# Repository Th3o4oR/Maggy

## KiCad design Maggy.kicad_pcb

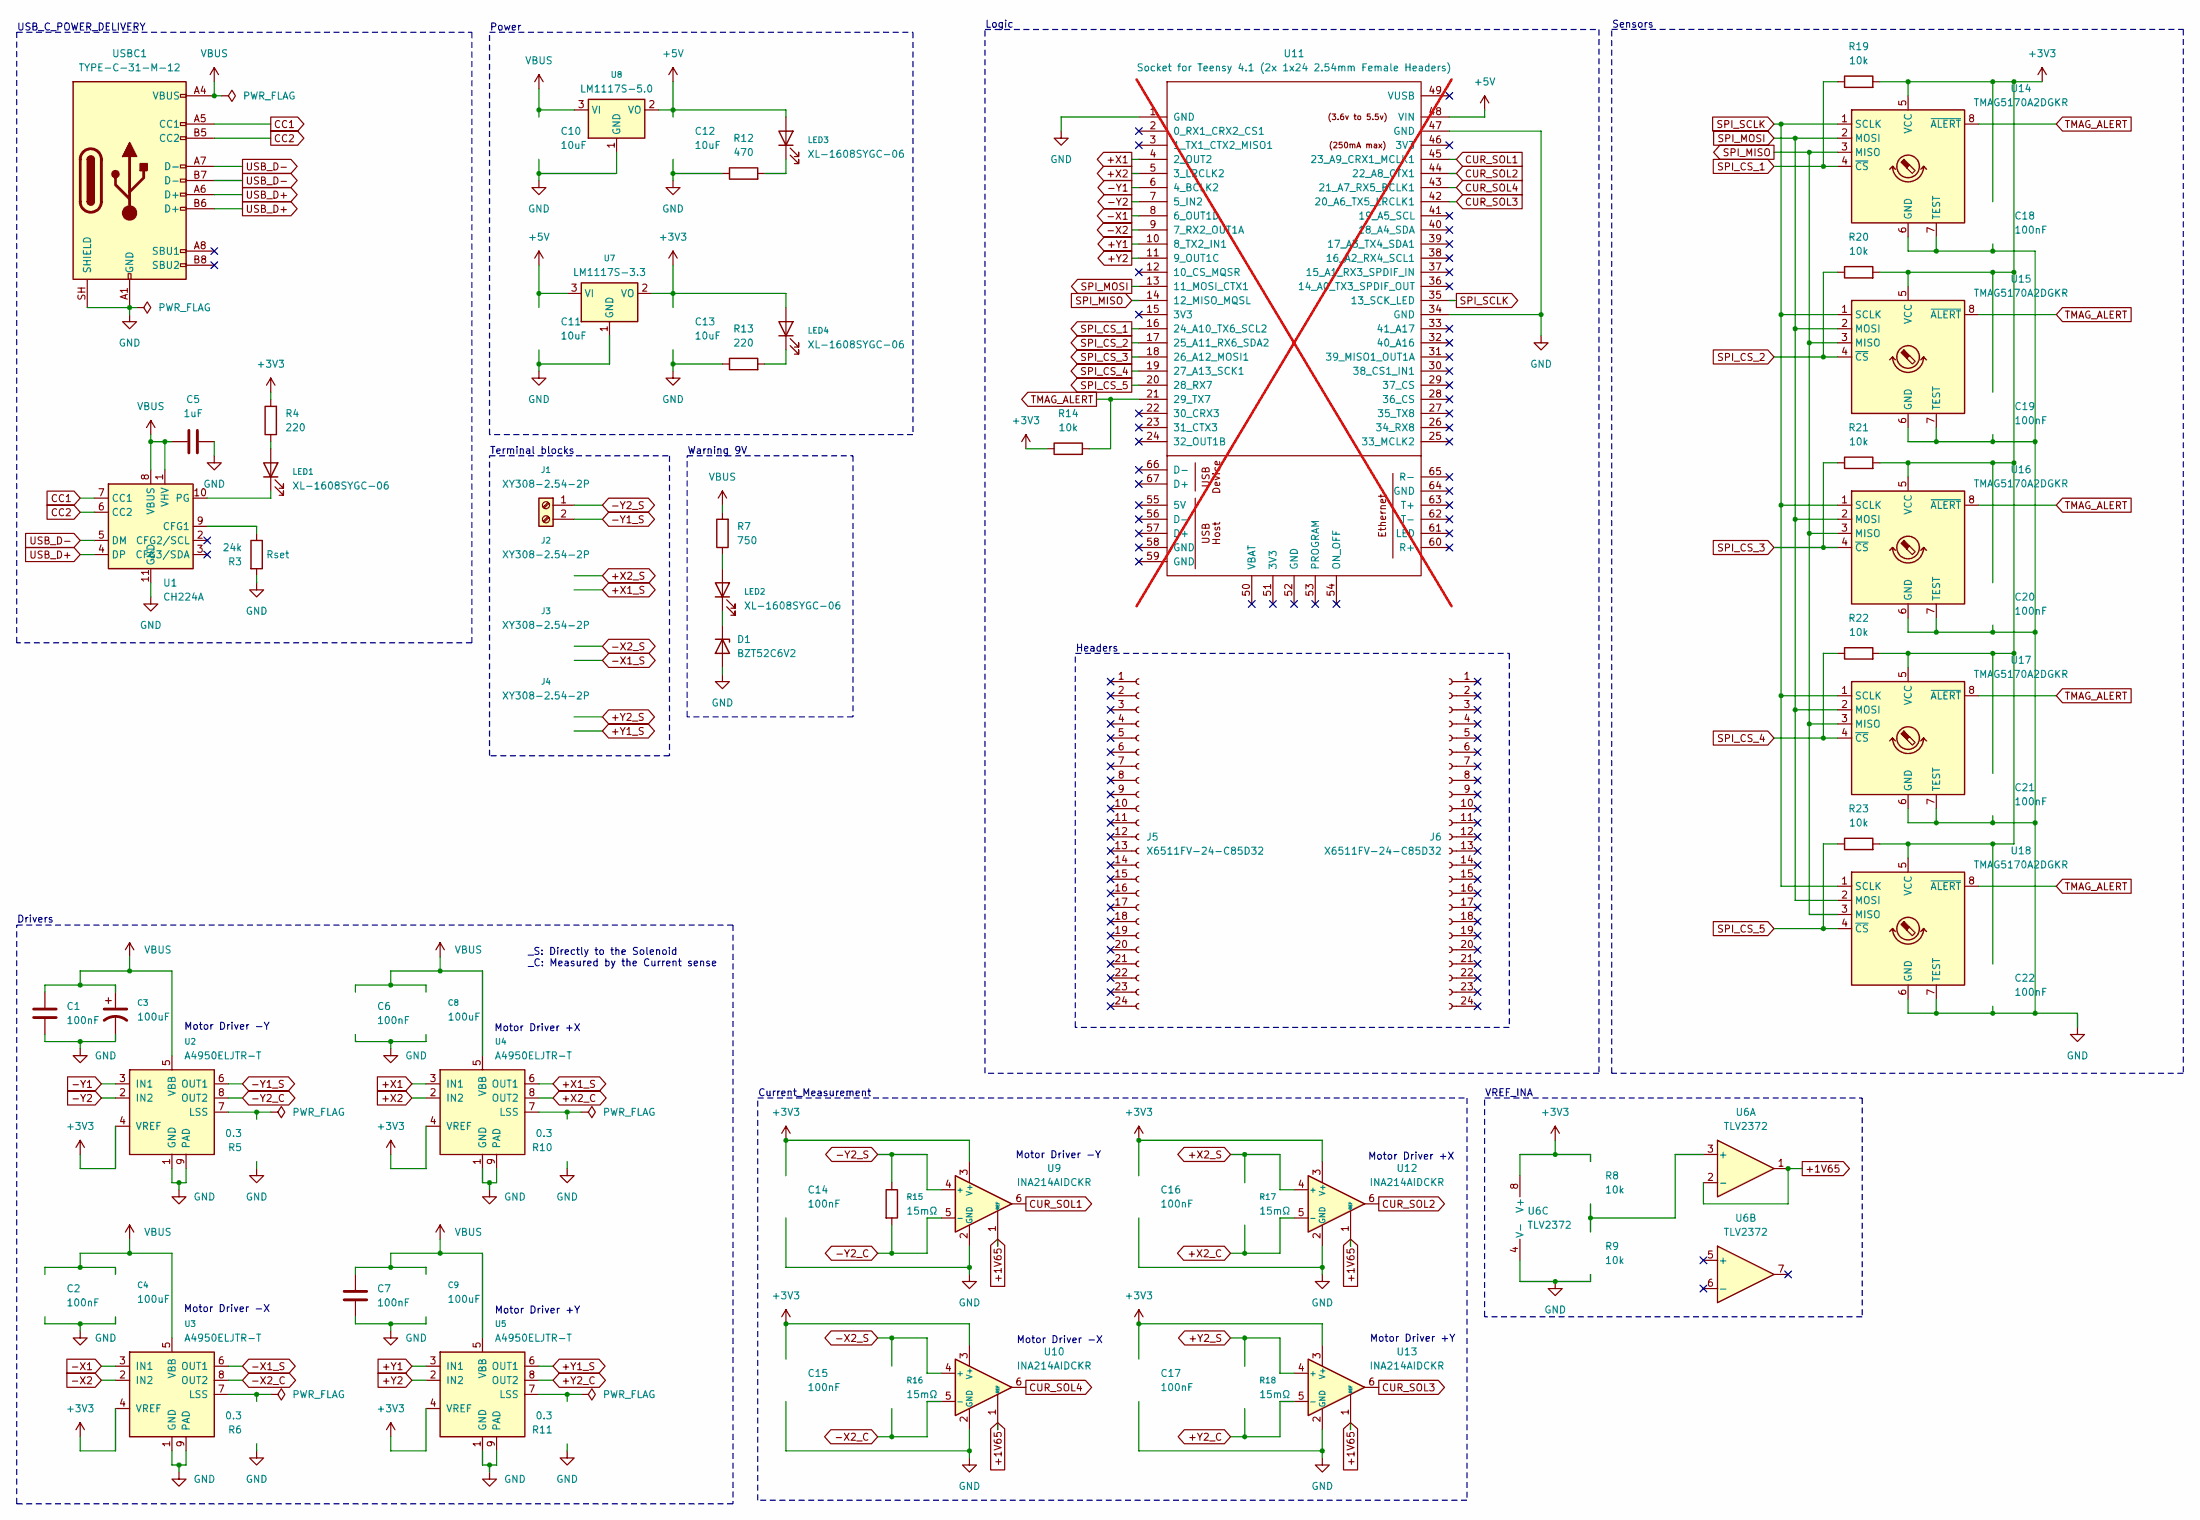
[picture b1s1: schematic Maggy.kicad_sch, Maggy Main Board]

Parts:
C1, C2, C6, C7, C14, C15, C16, C17, C18, C19, C20, C21, C22: 100nF; C_0603_1608Metric; LCSC C14663
C3, C4, C8, C9: 100uF; C_Elec_6.3x7.7; Manufacturer Part RST100UF35V009; LCSC Part Name 100uF ±20% 35V
C5: 1uF; C_0805_2012Metric; LCSC C28323
C10, C11, C12, C13: 10uF; C_0805_2012Metric; LCSC C15850
D1: BZT52C6V2; D_SOD-123; Manufacturer Part BZT52C6V2; LCSC Part Name BZT52C6V2
J1, J2, J3, J4: XY308-2.54-2P; TerminalBlock_Xinya_XY308-2.54-2P_1x02_P2.54mm_Horizontal; Manufacturer Part XY308-2.54-2P; LCSC Part Name 2.54mm 1x2P 排数:1 每排P数:2 直插
J5, J6: X6511FV-24-C85D32; PinHeader_1x24_P2.54mm_Vertical_NO_PADS; Manufacturer Part X6511FV-24-C85D32; LCSC C2883741
LED1: XL-1608SYGC-06; LED_0603_1608Metric; Manufacturer Part XL-1608SYGC-06; LCSC C965805
LED2, LED3, LED4: XL-1608SYGC-06; LED_0603_1608Metric; Manufacturer Part XL-1608SYGC-06; LCSC Part Name XL-1608SYGC-06
R3: 24k; R_0805_2012Metric; LCSC C17575
R4, R13: 220; R_0805_2012Metric; LCSC C17557
R5, R6, R10, R11: 0.3; R_1206_3216Metric; LCSC C59882
R7: 750; R_0805_2012Metric; LCSC C17818
R8, R9, R14, R19, R20, R21, R22, R23: 10k; R_0805_2012Metric; LCSC C17414
R12: 470; R_0805_2012Metric; LCSC C17710
R15, R16, R17, R18: 15mΩ; R_1206_3216Metric; Manufacturer Part 1206W3F150MT5E; LCSC Part Name RES 15mΩ ±1% 333mW 1206
U1: CH224A; SSOP-10-1EP_3.9x4.9mm_P1mm_EP2.1x3.3mm_ThermalVias; LCSC C42459160
U2, U3, U4, U5: A4950ELJTR-T; SOIC-8-1EP_3.9x4.9mm_P1.27mm_EP2.41x3.3mm_ThermalVias; Manufacturer Part A4950ELJTR-T; LCSC Part Name A4950ELJTR-T
U6: TLV2372; SOIC-8_3.9x4.9mm_P1.27mm; Manufacturer Part TLV2372IDR; LCSC Part Name TLV2372IDR
U7: LM1117S-3.3; SOT-223-3_TabPin2; Manufacturer Part LM1117S-3.3; LCSC Part Name 输入12V 输出3.3V 1A
U8: LM1117S-5.0; SOT-223-3_TabPin2; Manufacturer Part LM1117S-5.0; LCSC Part Name 输入12V 输出5V 1A
U9, U10, U12, U13: INA214AIDCKR; SOT-363_SC-70-6; Manufacturer Part INA214AIDCKR; LCSC Part Name INA214AIDCKR
U11: Socket for Teensy 4.1 (2x 1x24 2.54mm Female Head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; Teensy41_Socket_Only; not fitted
U14, U15, U16, U17, U18: TMAG5170A2DGKR; TMAG5170_Origin_Shifted_VSSOP-8_3x3mm_P0.65mm; LCSC C3716101
USBC1: TYPE-C-31-M-12; USB_C_Receptacle_HRO_TYPE-C-31-M-12; LCSC C165948

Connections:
+1V65: U6.1, U6.2 (-), U9.1 (REF), U10.1 (REF), U12.1 (REF), U13.1 (REF); also elsewhere on the board
+3V3: C13.2, C14.1, C15.1, C16.1, C17.1, C18.1, C19.1, C20.1, C21.1, C22.1, LED4.2 (A), R4.2, R8.2, R14.1, R19.2, R20.2, R21.2, R22.2, R23.2, U2.4 (VREF), U3.4 (VREF), U4.4 (VREF), U5.4 (VREF), U6.8 (V+), U7.2 (VO), U9.3 (V+), U10.3 (V+), U12.3 (V+), U13.3 (V+), U14.5 (VCC), U15.5 (VCC), U16.5 (VCC), U17.5 (VCC), U18.5 (VCC); also elsewhere on the board
+5V: C11.2, C12.2, LED3.2 (A), U7.3 (VI), U8.2 (VO), U11.48 (VIN); also elsewhere on the board
+X1: U4.3 (IN1), U11.4 (2_OUT2)
+X1_S: J2.2, U4.6 (OUT1)
+X2: U4.2 (IN2), U11.5 (3_LRCLK2)
+X2_C: R17.2, U4.8 (OUT2), U12.5 (-)
+X2_S: J2.1, R17.1, U12.4 (+)
+Y1: U5.3 (IN1), U11.10 (8_TX2_IN1)
+Y1_S: J4.2, U5.6 (OUT1)
+Y2: U5.2 (IN2), U11.11 (9_OUT1C)
+Y2_C: R18.2, U5.8 (OUT2), U13.5 (-)
+Y2_S: J4.1, R18.1, U13.4 (+)
-X1: U3.3 (IN1), U11.8 (6_OUT1D)
-X1_S: J3.2, U3.6 (OUT1)
-X2: U3.2 (IN2), U11.9 (7_RX2_OUT1A)
-X2_C: R16.2, U3.8 (OUT2), U10.5 (-)
-X2_S: J3.1, R16.1, U10.4 (+)
-Y1: U2.3 (IN1), U11.6 (4_BCLK2)
-Y1_S: J1.2, U2.6 (OUT1)
-Y2: U2.2 (IN2), U11.7 (5_IN2)
-Y2_C: R15.2, U2.8 (OUT2), U9.5 (-)
-Y2_S: J1.1, R15.1, U9.4 (+)
CC1: U1.7 (CC1), USBC1.A5 (CC1)
CC2: U1.6 (CC2), USBC1.B5 (CC2)
CUR_SOL1: U9.6, U11.45 (23_A9_CRX1_MCLK1)
CUR_SOL2: U11.44 (22_A8_CTX1), U12.6
CUR_SOL3: U11.42 (20_A6_TX5_LRCLK1), U13.6
CUR_SOL4: U10.6, U11.43 (21_A7_RX5_BCLK1)
GND: C1.1, C2.1, C3.2, C4.2, C5.1, C6.1, C7.1, C8.2, C9.2, C10.1, C11.1, C12.1, C13.1, C14.2, C15.2, C16.2, C17.2, C18.2, C19.2, C20.2, C21.2, C22.2, D1.2 (A), R3.2, R5.1, R6.1, R9.1, R10.1, R11.1, R12.1, R13.1, U1.11 (GND), U2.1 (GND), U2.9 (PAD), U3.1 (GND), U3.9 (PAD), U4.1 (GND), U4.9 (PAD), U5.1 (GND), U5.9 (PAD), U6.4 (V-), U7.1 (GND), U8.1 (GND), U9.2 (GND), U10.2 (GND), U11.1 (GND), U11.34 (GND), U11.47 (GND), U12.2 (GND), U13.2 (GND), U14.6 (GND), U14.7 (TEST), U15.6 (GND), U15.7 (TEST), U16.6 (GND), U16.7 (TEST), U17.6 (GND), U17.7 (TEST), U18.6 (GND), U18.7 (TEST), USBC1.A1 (GND), USBC1.A12 (GND), USBC1.B1 (GND), USBC1.B12 (GND), USBC1.SH (SHIELD)
unnamed: D1.1 (K), LED2.1 (K)
unnamed: LED1.2 (A), R4.1
unnamed: LED1.1 (K), U1.10 (PG)
unnamed: LED2.2 (A), R7.1
unnamed: LED3.1 (K), R12.2
unnamed: LED4.1 (K), R13.2
unnamed: R3.1, U1.9 (CFG1)
unnamed: R5.2, U2.7 (LSS)
unnamed: R6.2, U3.7 (LSS)
unnamed: R10.2, U4.7 (LSS)
unnamed: R11.2, U5.7 (LSS)
unnamed: R8.1, R9.2, U6.3 (+)
SPI_CS_1: R19.1, U11.16 (24_A10_TX6_SCL2), U14.4 (~CS)
SPI_CS_2: R20.1, U11.17 (25_A11_RX6_SDA2), U15.4 (~CS)
SPI_CS_3: R21.1, U11.18 (26_A12_MOSI1), U16.4 (~CS)
SPI_CS_4: R22.1, U11.19 (27_A13_SCK1), U17.4 (~CS)
SPI_CS_5: R23.1, U11.20 (28_RX7), U18.4 (~CS)
SPI_MISO: U11.14 (12_MISO_MQSL), U14.3 (MISO), U15.3 (MISO), U16.3 (MISO), U17.3 (MISO), U18.3 (MISO); also elsewhere on the board
SPI_MOSI: U11.13 (11_MOSI_CTX1), U14.2 (MOSI), U15.2 (MOSI), U16.2 (MOSI), U17.2 (MOSI), U18.2 (MOSI); also elsewhere on the board
SPI_SCLK: U11.35 (13_SCK_LED), U14.1 (SCLK), U15.1 (SCLK), U16.1 (SCLK), U17.1 (SCLK), U18.1 (SCLK); also elsewhere on the board
TMAG_ALERT: R14.2, U11.21 (29_TX7), U14.8 (~ALERT), U15.8 (~ALERT), U16.8 (~ALERT), U17.8 (~ALERT), U18.8 (~ALERT)
USB_D+: U1.4 (DP), USBC1.A6 (D+), USBC1.B6 (D+)
USB_D-: U1.5 (DM), USBC1.A7 (D-), USBC1.B7 (D-)
VBUS: C1.2, C2.2, C3.1, C4.1, C5.2, C6.2, C7.2, C8.1, C9.1, C10.2, R7.2, U1.1 (VHV), U1.8 (VBUS), U2.5 (VBB), U3.5 (VBB), U4.5 (VBB), U5.5 (VBB), U8.3 (VI), USBC1.A4 (VBUS), USBC1.A9 (VBUS), USBC1.B4 (VBUS), USBC1.B9 (VBUS); also elsewhere on the board

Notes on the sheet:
Terminal blocks
Motor Driver +X
USB_C_POWER_DELIVERY
Warning 9V
Motor Driver -X
Sensors
Motor Driver +Y
Headers
Logic
Motor Driver -Y
VREF_INA
Power
Current_Measurement
_S: Directly to the Solenoid _C: Measured by the Current sense
Drivers

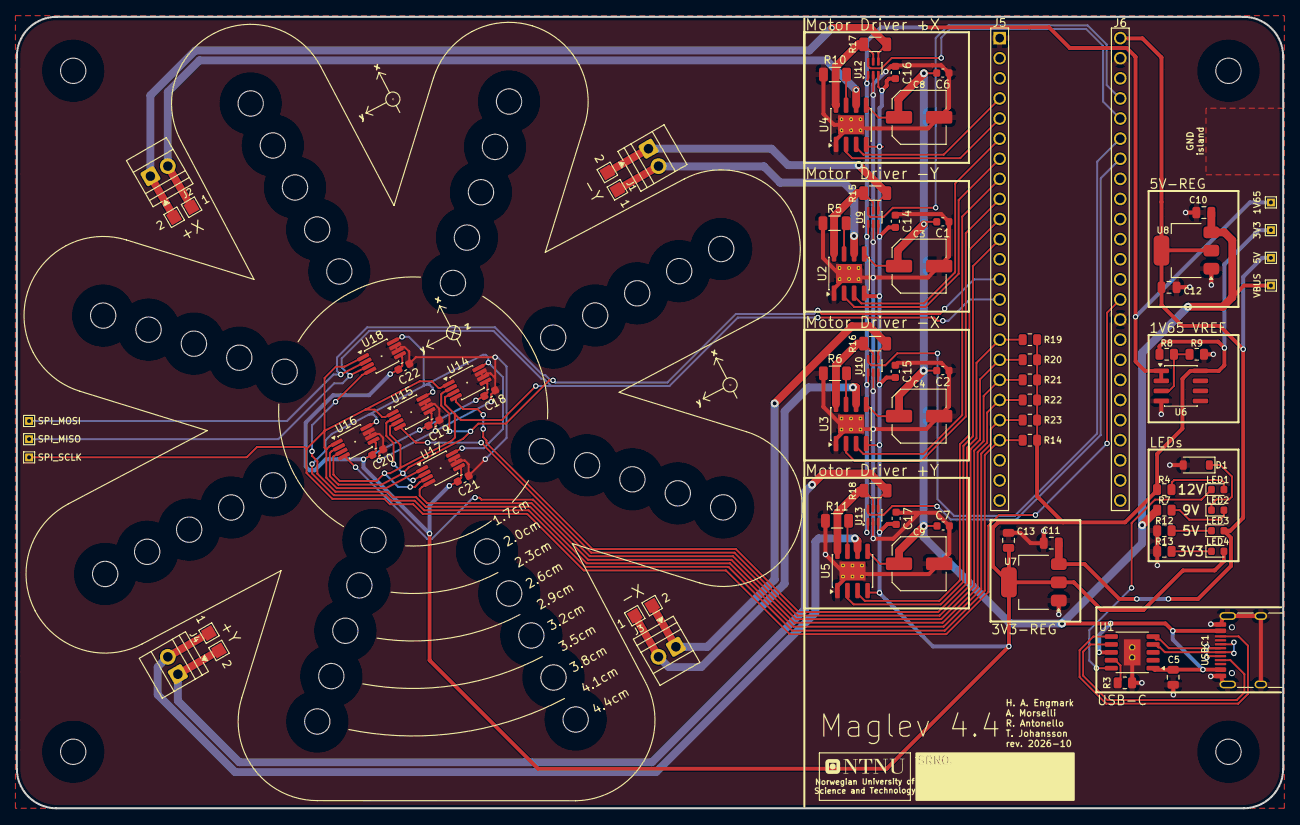
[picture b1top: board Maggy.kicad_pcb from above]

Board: 2 copper layers, 160.0 x 100.0 mm, 80 parts (0 on the bottom side), 54 nets.

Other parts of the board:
1V65, 3V3, 5V: TestPoint_THTPad_1.0x1.0mm_Drill0.5mm
SPI_MISO: TestPoint_THTPad_1.0x1.0mm_Drill0.5mm
SPI_MOSI: TestPoint_THTPad_1.0x1.0mm_Drill0.5mm
SPI_SCLK: TestPoint_THTPad_1.0x1.0mm_Drill0.5mm
VBUS: TestPoint_THTPad_1.0x1.0mm_Drill0.5mm

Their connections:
+1V65: 1V65.1; also elsewhere on the board
+3V3: 3V3.1; also elsewhere on the board
+5V: 5V.1; also elsewhere on the board
SPI_MISO: SPI_MISO.1; also elsewhere on the board
SPI_MOSI: SPI_MOSI.1; also elsewhere on the board
SPI_SCLK: SPI_SCLK.1; also elsewhere on the board
VBUS: VBUS.1; also elsewhere on the board

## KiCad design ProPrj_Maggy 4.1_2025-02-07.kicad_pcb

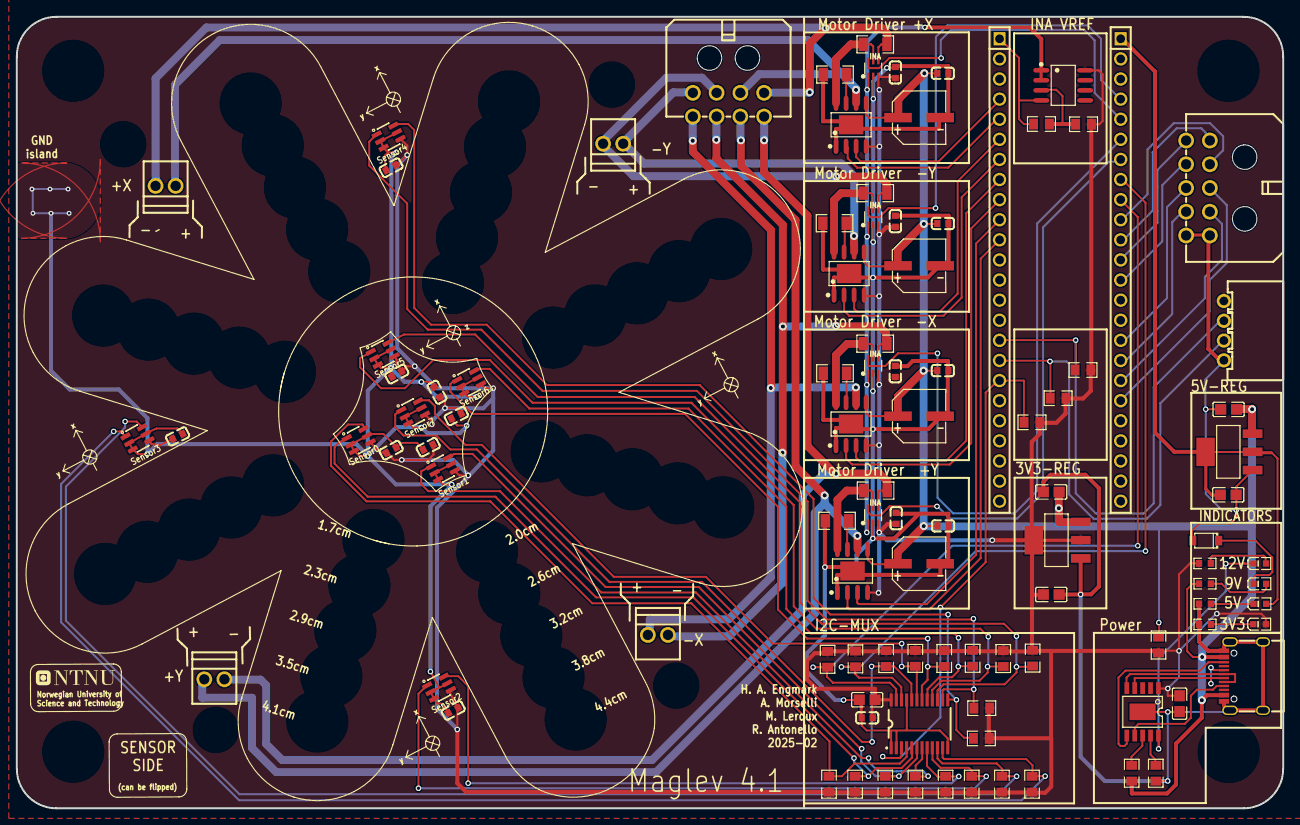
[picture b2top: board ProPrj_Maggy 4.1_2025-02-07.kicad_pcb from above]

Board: 2 copper layers, 160.0 x 100.0 mm, 101 parts (0 on the bottom side), 75 nets.

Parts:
C1, C2, C3, C4, C6, C27: C0805
C5, C7, C8, C9, C10, C11, C12, C13, C14, C15, C17, C19, C21, C23, C24, C25, C26: C0603
C16, C18, C20, C22: CAP-SMD_BD6.3-L6.6-W6.6-LS7.2-FD
CN1: CONN-TH_43045-1000
CN2: CONN-TH_0430450800
LED1, LED2, LED3, LED4: LED0603-RD_GREEN
R1, R2, R6, R7, R8, R9, R10, R11, R12, R13, R14, R15, R16, R17, R18, R19, R20, R21, R26, R27, R29, R32, R33, R34, R39, R40: R0805
R3, R4, R5, R28: R0603
R22, R23, R24, R25, R35, R36, R37, R38: R1206
U1, U2: SOT-223-3_L6.5-W3.4-P2.30-LS7.0-BR
U3: ESSOP-10_L4.9-W3.9-P1.0-LS6.0-TL-EP
U4, U5: HDR-TH_24P-P2.54-V-F
U6: CONN-TH_XH2.54-4AW
U7: TSSOP-24_L7.8-W4.4-P0.65-LS6.4-BL
U10, U11, U12, U13, U14, U15, U16, U17: SOP-6_L3.0-W1.5-P0.95-LS2.5-BR
U20, U21, U22, U23: SOIC-8_L4.9-W3.9-P1.27-LS6.0-BL-EP
U27: SOD-123_L2.7-W1.6-LS3.7-RD
U30, U31, U32, U33: SC-70-6_L2.2-W1.3-P0.65-LS2.2-BR
U40: SOIC-8_L4.9-W3.9-P1.27-LS6.0-BL
U50, U51, U52, U53: CONN-TH_XY308-2.54-2P
USBC1: USB-C_SMD-TYPE-C-31-M-12

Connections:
1V65: U30.1, U31.1, U32.1, U33.1, U40.1, U40.2
1_1: CN2.1, U20.6, U50.1
1_21: CN2.2, R35.2, U30.4, U50.2
1_22: R35.1, U20.8, U30.5
2_1: CN2.3, U21.6, U51.1
2_21: CN2.4, R36.2, U31.4, U51.2
2_22: R36.1, U21.8, U31.5
3V3: C4.1, C5.1, C6.2, C7.1, C8.1, C9.1, C10.1, C11.1, C12.1, C13.1, C14.1, C23.2, C24.2, C25.2, C26.2, C27.1, LED1.2, R1.2, R2.2, R6.2, R7.2, R8.2, R9.2, R10.2, R11.2, R12.2, R13.2, R14.2, R15.2, R16.2, R17.2, R18.2, R19.2, R20.2, R21.2, R27.1, R28.2, R32.1, R33.1, R34.1, R39.2, U2.2, U2.4, U3.1, U6.1, U7.24, U10.4, U11.4, U12.4, U13.4, U14.4, U15.4, U16.4, U17.4, U20.4, U21.4, U22.4, U23.4, U30.3, U31.3, U32.3, U33.3, U40.8
3_1: CN2.7, U23.6, U53.1
3_21: CN2.8, R38.2, U33.4, U53.2
3_22: R38.1, U23.8, U33.5
4_1: CN2.5, U22.6, U52.1
4_21: CN2.6, R37.2, U32.4, U52.2
4_22: R37.1, U22.8, U32.5
$1N3748: R22.2, U20.7
$1N3820: LED2.1, R4.2
$1N3821: LED1.1, R3.2
$1N8157: R26.1, U3.9
$1N8202: R29.1, U3.8
$1N8651: R23.2, U21.7
$1N8936: R24.2, U22.7
$1N9221: R25.2, U23.7
$1N10392: LED4.1, U3.10
$1N10465: LED4.2, R28.1
$1N10718: LED3.1, U27.1
$1N10720: LED3.2, R5.1
$1N18521: R39.1, R40.2, U40.3
+5V: C2.1, LED2.2, U1.2, U1.4, U5.1
CC1: U3.7, USBC1.A5
CC2: U3.6, USBC1.B5
CUR_SOL1: U5.4, U30.6
CUR_SOL2: U5.5, U31.6
CUR_SOL3: U5.7, U33.6
CUR_SOL4: U5.6, U32.6
DM: U3.5, USBC1.A7, USBC1.B7
DP: U3.4, USBC1.A6, USBC1.B6
GND: C1.2, C2.2, C3.2, C4.2, C5.2, C6.1, C7.2, C8.2, C9.2, C10.2, C11.2, C12.2, C13.2, C14.2, C15.2, C16.2, C17.2, C18.2, C19.2, C20.2, C21.2, C22.2, C23.1, C24.1, C25.1, C26.1, C27.2, CN1.5, CN1.10, R3.1, R4.1, R22.1, R23.1, R24.1, R25.1, R26.2, R40.1, U1.1, U2.1, U3.11, U4.1, U5.2, U5.15, U6.4, U7.1, U7.2, U7.12, U7.21, U10.2, U10.3, U10.5, U11.2, U11.3, U11.5, U12.2, U12.3, U12.5, U13.2, U13.3, U13.5, U14.2, U14.3, U14.5, U15.2, U15.3, U15.5, U16.2, U16.3, U16.5, U17.2, U17.3, U17.5, U20.1, U20.9, U21.1, U21.9, U22.1, U22.9, U23.1, U23.9, U27.2, U30.2, U31.2, U32.2, U33.2, U40.4, USBC1.0, USBC1.1, USBC1.2, USBC1.3, USBC1.A1, USBC1.A12, USBC1.B1, USBC1.B12
HB_0A: U4.6, U20.3
HB_0B: U4.7, U20.2
HB_1A: U4.4, U21.3
HB_1B: U4.5, U21.2
HB_2A: U4.10, U23.3
HB_2B: U4.11, U23.2
HB_3A: U4.8, U22.3
HB_3B: U4.9, U22.2
I2C_RST: R32.2, U4.18, U7.3
I2C_SCL: R2.1, U5.8, U7.22
I2C_SCL2: R34.2, U4.16, U6.2
I2C_SDA: R1.1, U5.9, U7.23
I2C_SDA2: R33.2, U4.17, U6.3
SCL0: R7.1, U7.5, U10.1
SCL1: R9.1, U7.7, U11.1
SCL2: R11.1, U7.9, U12.1
SCL3: R13.1, U7.11, U13.1
SCL4: R15.1, U7.14, U14.1
SCL5: R17.1, U7.16, U15.1
SCL6: R19.1, U7.18, U16.1
SCL7: R21.1, U7.20, U17.1
SDA0: R6.1, U7.4, U10.6
SDA1: R8.1, U7.6, U11.6
SDA2: R10.1, U7.8, U12.6
SDA3: R12.1, U7.10, U13.6
SDA4: R14.1, U7.13, U14.6
SDA5: R16.1, U7.15, U15.6
SDA6: R18.1, U7.17, U16.6
SDA7: R20.1, U7.19, U17.6
UX_N_IN: CN1.9, U5.17
UX_N_OUT: CN1.1, U5.11
UX_P_IN: CN1.8, U5.16
UX_P_OUT: CN1.2, U5.10
UY_N_IN: CN1.3, U5.19
UY_N_OUT: CN1.7, U5.13
UY_P_IN: CN1.4, U5.18
UY_P_OUT: CN1.6, U5.12
VBUS: C1.1, C3.1, C15.1, C16.1, C17.1, C18.1, C19.1, C20.1, C21.1, C22.1, R5.2, R27.2, R29.2, U1.3, U2.3, U20.5, U21.5, U22.5, U23.5, USBC1.A4, USBC1.A9, USBC1.B4, USBC1.B9
